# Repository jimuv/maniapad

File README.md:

# maniapad

### Inspiration

I wanted to create a macropad that would allow me to play 4 key Vertical Scrolling Rhythm Games. I created a macropad using 4 switches.

### Challenges

Although I had some beginner experiences in SolidWorks, I have not fully developed the skills needed for 3D CAD, which in addition to this, was having to migrate to Fusion 360, which is similar, though it threw me off a bit. I had to go step by step as well as trying to find the tools needed to start modeling. A lot of these tools are scattered to me as I do not have the muscle memory or actual memory of where tools are usually placed, such as sketching or changing my views.

### Specifications

BOM: 
- 4x Cherry MX Switches
- 1x XIAO RP2040
- 4x Blank DSA Keycaps
- 4x M3x16 Bolt
- 4x M3 Heatset

Others:
- KMK Firmware
- Top Case.stl 
- Bottom Case.stl

Schematic            |  PCB         |   Case Bottom         |   Case Top         |   Case Full
:-------------------------:|:-------------------------:|:-------------------------:|:-------------------------:|:-------------------------:|
    |    |   |   |

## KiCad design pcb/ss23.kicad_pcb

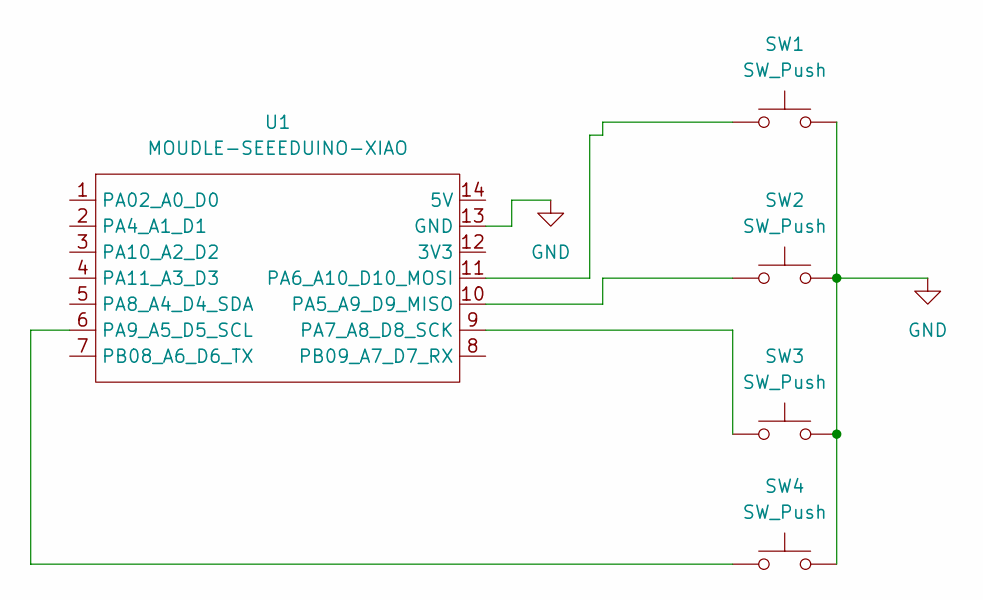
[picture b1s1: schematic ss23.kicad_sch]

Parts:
SW1, SW2, SW3, SW4: SW_Push; SW_Cherry_MX_1.00u_PCB
U1: MOUDLE-SEEEDUINO-XIAO; XIAO-Generic-Hybrid-14P-2.54-21X17.8MM

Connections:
GND: SW1.2, SW2.2, SW3.2, SW4.2, U1.13 (GND)
unnamed: SW2.1, U1.10 (PA5_A9_D9_MISO)
unnamed: SW1.1, U1.11 (PA6_A10_D10_MOSI)
unnamed: SW3.1, U1.9 (PA7_A8_D8_SCK)
unnamed: SW4.1, U1.6 (PA9_A5_D5_SCL)

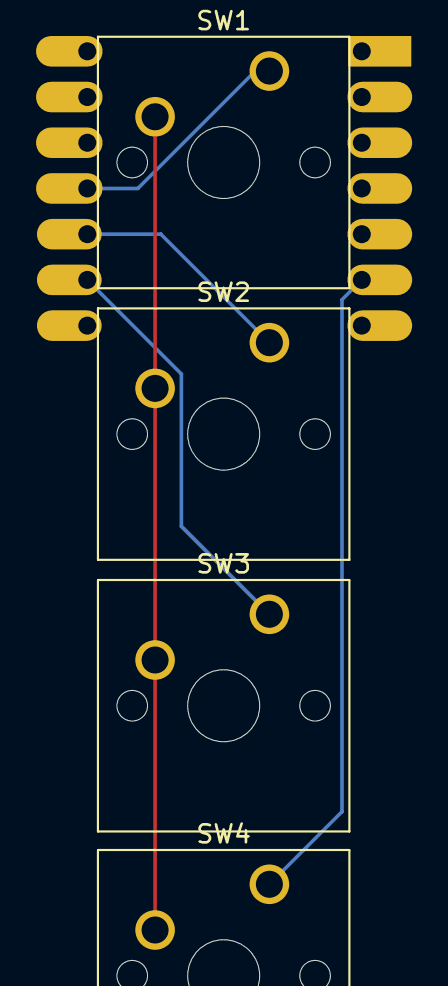
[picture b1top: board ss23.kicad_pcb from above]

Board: 2 copper layers, 5 parts (1 on the bottom side), 5 nets.

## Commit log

2026-06-12 Create CAD
2026-06-12 add pcb files
